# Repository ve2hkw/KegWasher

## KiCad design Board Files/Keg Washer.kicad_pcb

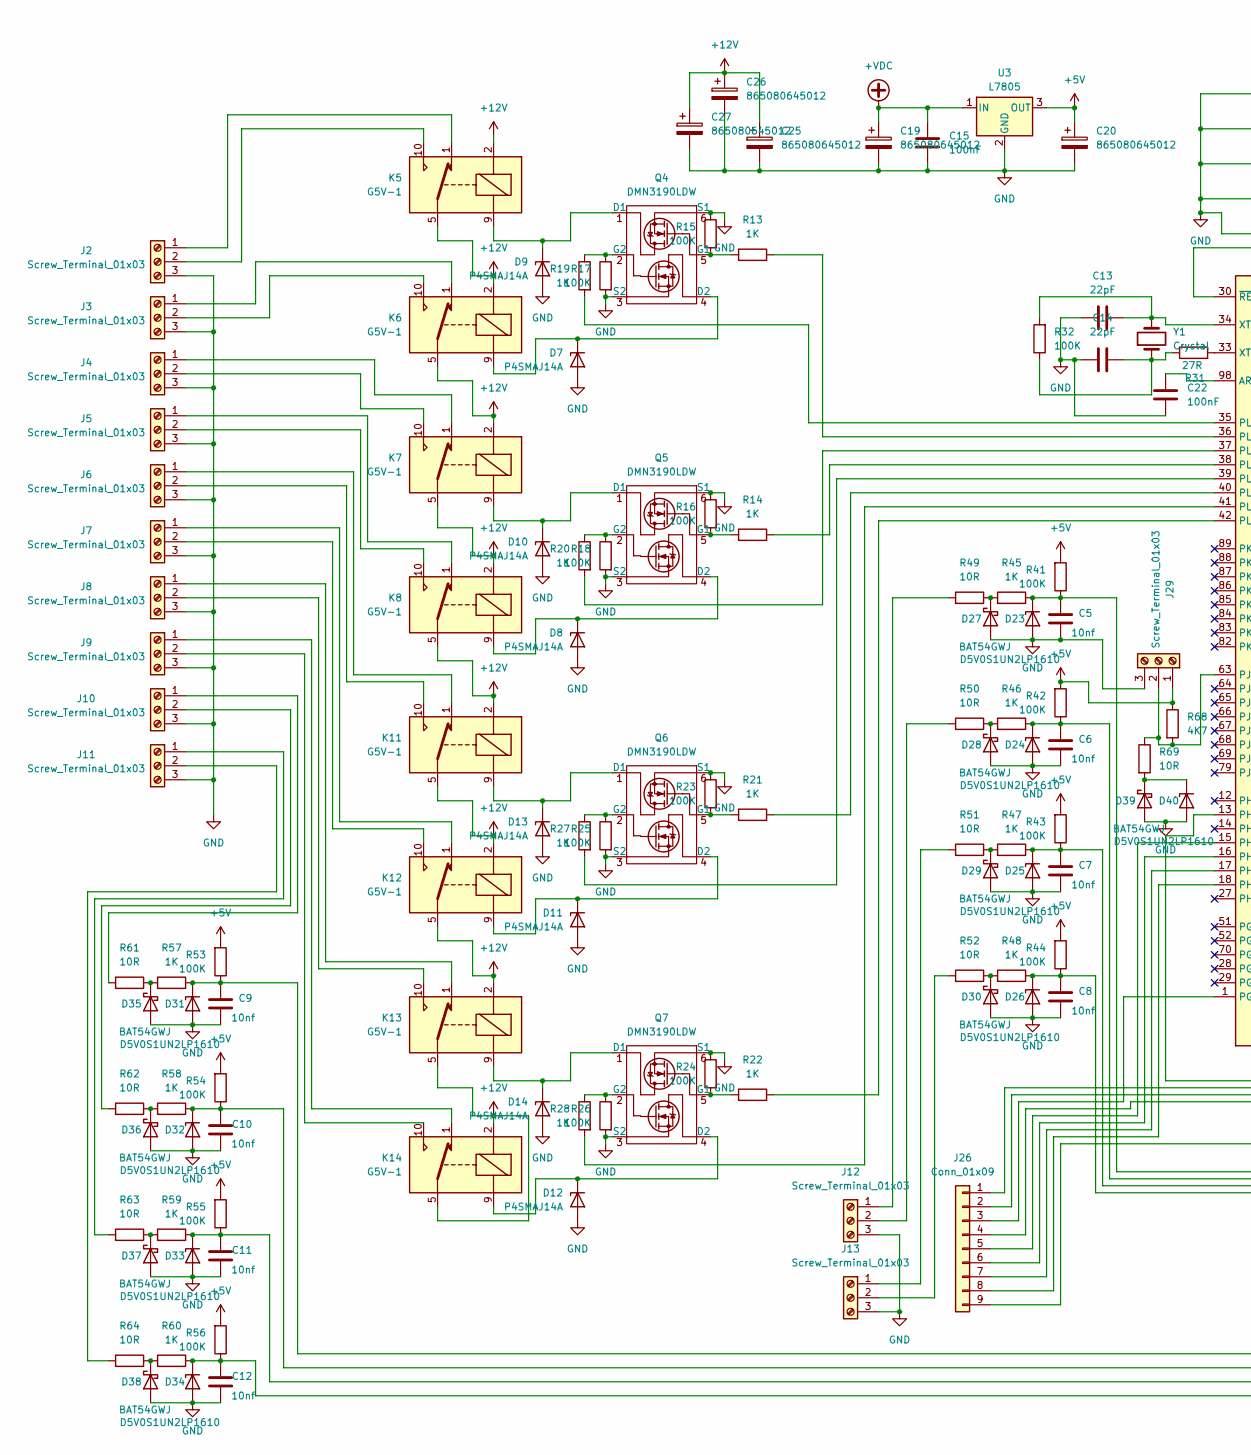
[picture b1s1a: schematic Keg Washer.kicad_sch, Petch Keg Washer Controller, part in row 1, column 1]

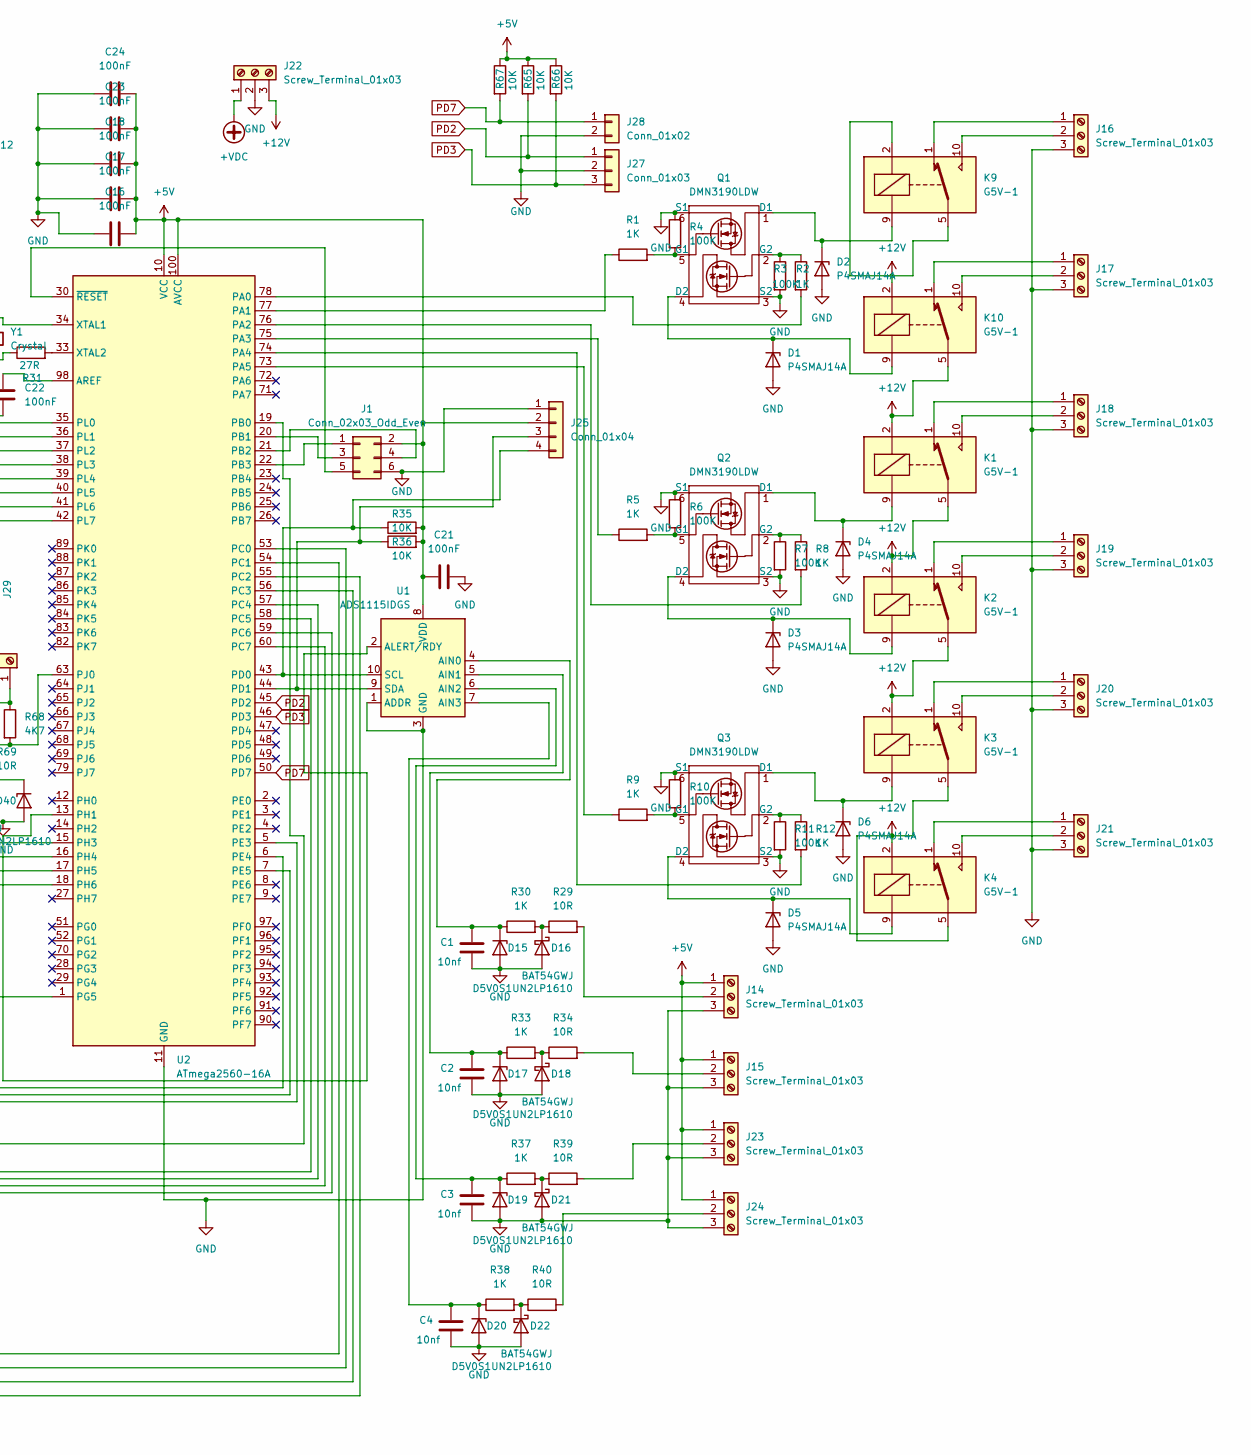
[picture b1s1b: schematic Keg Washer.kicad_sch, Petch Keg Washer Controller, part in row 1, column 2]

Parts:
C1, C2, C3, C4, C5, C6, C7, C8, C9, C10, C11, C12: 10nf; C_0805_2012Metric
C13, C14: 22pF; C_0805_2012Metric
C15, C16, C17, C18, C21, C22, C23, C24: 100nF; C_0805_2012Metric
C19, C20, C25, C26, C27: 865080645012; CP_Elec_6.3x7.7
D1, D2, D3, D4, D5, D6, D7, D8, D9, D10, D11, D12, D13, D14: P4SMAJ14A; D_SMA
D15, D17, D19, D20, D23, D24, D25, D26, D31, D32, D33, D34, D40: D5V0S1UN2LP1610; D_0603_1608Metric
D16, D18, D21, D22, D27, D28, D29, D30, D35, D36, D37, D38, D39: BAT54GWJ; D_SOD-123
J1: Conn_02x03_Odd_Even; PinHeader_2x03_P2.54mm_Vertical
J2, J3, J4, J5, J6, J7, J8, J9, J10, J11, J12, J13, J14, J15, J16, J17, J18, J19, J20, J21, J22, J23, J24, J29: Screw_Terminal_01x03; Altech_AK100_1x03_P5.00mm
J25: Conn_01x04; PinHeader_1x04_P2.54mm_Vertical
J26: Conn_01x09; PinHeader_1x09_P2.54mm_Vertical
J27: Conn_01x03; PinHeader_1x03_P2.54mm_Vertical
J28: Conn_01x02; PinHeader_1x02_P2.54mm_Vertical
K1, K2, K3, K4, K5, K6, K7, K8, K9, K10, K11, K12, K13, K14: G5V-1; Relay_SPDT_Omron_G5V-1
Q1, Q2, Q3, Q4, Q5, Q6, Q7: DMN3190LDW; SOT-363_SC-70-6
R1, R2, R5, R8, R9, R12, R13, R14, R19, R20, R21, R22, R27, R28, R30, R33, R37, R38, R45, R46, R47, R48, R57, R58, R59, R60: 1K; R_0805_2012Metric
R3, R4, R6, R7, R10, R11, R15, R16, R17, R18, R23, R24, R25, R26, R32, R41, R42, R43, R44, R53, R54, R55, R56: 100K; R_0805_2012Metric
R29, R34, R39, R40, R49, R50, R51, R52, R61, R62, R63, R64, R69: 10R; R_0805_2012Metric
R31: 27R; R_0805_2012Metric
R35, R36, R65, R66, R67: 10K; R_0805_2012Metric
R68: 4K7; R_0805_2012Metric
U1: ADS1115IDGS; TSSOP-10_3x3mm_P0.5mm
U2: ATmega2560-16A; TQFP-100_14x14mm_P0.5mm
U3: L7805; TO-220F-3_Vertical
Y1: Crystal; Crystal_SMD_ECS_CSM3X-2Pin_7.6x4.1mm

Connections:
+5V: C16.2, C17.2, C18.2, C20.1, C21.1, C23.2, C24.2, J1.2, J14.1, J15.1, J23.1, J24.1, J25.2, J29.1, R35.2, R36.2, R41.2, R42.2, R43.2, R44.2, R53.2, R54.2, R55.2, R56.2, R65.1, R66.1, R67.1, R68.1, U1.8 (VDD), U2.10 (VCC), U2.31 (VCC), U2.61 (VCC), U2.80 (VCC), U2.100 (AVCC), U3.3 (OUT)
+12V: C25.1, C26.1, C27.1, J22.3, K1.2, K1.5, K1.6, K2.2, K2.5, K2.6, K3.2, K3.5, K3.6, K4.2, K4.5, K4.6, K5.2, K5.5, K5.6, K6.2, K6.5, K6.6, K7.2, K7.5, K7.6, K8.2, K8.5, K8.6, K9.2, K9.5, K9.6, K10.2, K10.5, K10.6, K11.2, K11.5, K11.6, K12.2, K12.5, K12.6, K13.2, K13.5, K13.6, K14.2, K14.5, K14.6
+VDC: C15.1, C19.1, J22.1, U3.1 (IN)
GND: C1.2, C2.2, C3.2, C4.2, C5.2, C6.2, C7.2, C8.2, C9.2, C10.2, C11.2, C12.2, C13.1, C14.1, C15.2, C16.1, C17.1, C18.1, C19.2, C20.2, C21.2, C22.1, C23.1, C24.1, C25.2, C26.2, C27.2, D1.2 (A), D2.2 (A), D3.2 (A), D4.2 (A), D5.2 (A), D6.2 (A), D7.2 (A), D8.2 (A), D9.2 (A), D10.2 (A), D11.2 (A), D12.2 (A), D13.2 (A), D14.2 (A), D15.2 (A), D16.2 (A), D17.2 (A), D18.2 (A), D19.2 (A), D20.2 (A), D21.2 (A), D22.2 (A), D23.2 (A), D24.2 (A), D25.2 (A), D26.2 (A), D27.2 (A), D28.2 (A), D29.2 (A), D30.2 (A), D31.2 (A), D32.2 (A), D33.2 (A), D34.2 (A), D35.2 (A), D36.2 (A), D37.2 (A), D38.2 (A), D39.2 (A), D40.2 (A), J1.6, J2.3, J3.3, J4.3, J5.3, J6.3, J7.3, J8.3, J9.3, J10.3, J11.3, J12.3, J13.3, J14.3, J15.3, J16.3, J17.3, J18.3, J19.3, J20.3, J21.3, J22.2, J23.3, J24.3, J25.1, J27.2, J28.2, J29.3, Q1.3 (S2), Q1.6 (S1), Q2.3 (S2), Q2.6 (S1), Q3.3 (S2), Q3.6 (S1), Q4.3 (S2), Q4.6 (S1), Q5.3 (S2), Q5.6 (S1), Q6.3 (S2), Q6.6 (S1), Q7.3 (S2), Q7.6 (S1), R3.2, R4.1, R6.1, R7.2, R10.1, R11.2, R15.1, R16.1, R17.2, R18.2, R23.1, R24.1, R25.2, R26.2, U1.1 (ADDR), U1.3 (GND), U2.11 (GND), U2.32 (GND), U2.62 (GND), U2.81 (GND), U2.99 (GND), U3.2 (GND)
unnamed: C14.2, R31.1, R32.1, Y1.1
unnamed: D1.1 (K), K10.9, Q1.4 (D2)
unnamed: D2.1 (K), K9.9, Q1.1 (D1)
unnamed: D3.1 (K), K2.9, Q2.4 (D2)
unnamed: D4.1 (K), K1.9, Q2.1 (D1)
unnamed: D5.1 (K), K4.9, Q3.4 (D2)
unnamed: D6.1 (K), K3.9, Q3.1 (D1)
unnamed: D7.1 (K), K6.9, Q4.4 (D2)
unnamed: D8.1 (K), K8.9, Q5.4 (D2)
unnamed: D9.1 (K), K5.9, Q4.1 (D1)
unnamed: D10.1 (K), K7.9, Q5.1 (D1)
unnamed: D11.1 (K), K12.9, Q6.4 (D2)
unnamed: D12.1 (K), K14.9, Q7.4 (D2)
unnamed: D13.1 (K), K11.9, Q6.1 (D1)
unnamed: D14.1 (K), K13.9, Q7.1 (D1)
unnamed: C1.1, D15.1 (K), R30.1, U1.4 (AIN0)
unnamed: D16.1 (K), R29.1, R30.2
unnamed: C2.1, D17.1 (K), R33.1, U1.5 (AIN1)
unnamed: D18.1 (K), R33.2, R34.1
unnamed: C3.1, D19.1 (K), R37.1, U1.6 (AIN2)
unnamed: C4.1, D20.1 (K), R38.1, U1.7 (AIN3)
unnamed: D21.1 (K), R37.2, R39.1
unnamed: D22.1 (K), R38.2, R40.1
unnamed: C5.1, D23.1 (K), R41.1, R45.1, U2.58 (PC5)
unnamed: C6.1, D24.1 (K), R42.1, R46.1, U2.57 (PC4)
unnamed: C7.1, D25.1 (K), R43.1, R47.1, U2.60 (PC7)
unnamed: C8.1, D26.1 (K), R44.1, R48.1, U2.59 (PC6)
unnamed: D27.1 (K), R45.2, R49.1
unnamed: D28.1 (K), R46.2, R50.1
unnamed: D29.1 (K), R47.2, R51.1
unnamed: D30.1 (K), R48.2, R52.1
unnamed: C9.1, D31.1 (K), R53.1, R57.1, U2.54 (PC1)
unnamed: C10.1, D32.1 (K), R54.1, R58.1, U2.53 (PC0)
unnamed: C11.1, D33.1 (K), R55.1, R59.1, U2.56 (PC3)
unnamed: C12.1, D34.1 (K), R56.1, R60.1, U2.55 (PC2)
unnamed: D35.1 (K), R57.2, R61.1
unnamed: D36.1 (K), R58.2, R62.1
unnamed: D37.1 (K), R59.2, R63.1
unnamed: D38.1 (K), R60.2, R64.1
unnamed: D39.1 (K), D40.1 (K), R69.2
unnamed: J1.1, U2.22 (PB3)
unnamed: J1.3, U2.20 (PB1)
unnamed: J1.4, U2.21 (PB2)
unnamed: J1.5, U2.30 (~RESET)
unnamed: J2.1, K5.1
unnamed: J2.2, K5.10
unnamed: J3.1, K6.1
unnamed: J3.2, K6.10
unnamed: J4.1, K7.1
unnamed: J4.2, K7.10
unnamed: J5.1, K8.1
unnamed: J5.2, K8.10
unnamed: J6.1, K11.1
unnamed: J6.2, K11.10
unnamed: J7.1, K12.1
unnamed: J7.2, K12.10
unnamed: J8.1, K13.1
unnamed: J8.2, K13.10
unnamed: J9.1, K14.1
unnamed: J9.2, K14.10
unnamed: J10.1, R61.2
unnamed: J10.2, R62.2
unnamed: J11.1, R63.2
unnamed: J11.2, R64.2
unnamed: J12.1, R49.2
unnamed: J12.2, R50.2
unnamed: J13.1, R51.2
unnamed: J13.2, R52.2
unnamed: J14.2, R29.2
unnamed: J15.2, R34.2
unnamed: J16.1, K9.1
unnamed: J16.2, K9.10
unnamed: J17.1, K10.1
unnamed: J17.2, K10.10
unnamed: J18.1, K1.1
unnamed: J18.2, K1.10
unnamed: J19.1, K2.1
unnamed: J19.2, K2.10
unnamed: J20.1, K3.1
unnamed: J20.2, K3.10
unnamed: J21.1, K4.1
unnamed: J21.2, K4.10
unnamed: J23.2, R39.2
unnamed: J24.2, R40.2
unnamed: J25.3, R36.1, U1.9 (SDA), U2.44 (PD1)
unnamed: J25.4, R35.1, U1.10 (SCL), U2.43 (PD0)
unnamed: J26.1, U2.6 (PE4)
unnamed: J26.2, U2.7 (PE5)
unnamed: J26.3, U2.1 (PG5)
unnamed: J26.4, U2.5 (PE3)
unnamed: J26.5, U2.15 (PH3)
unnamed: J26.6, U2.16 (PH4)
unnamed: J26.7, U2.17 (PH5)
unnamed: J26.8, U2.18 (PH6)
unnamed: J26.9, U2.19 (PB0)
unnamed: J29.2, R68.2, R69.1, U2.63 (PJ0)
unnamed: Q1.5 (G1), R1.2, R4.2
unnamed: Q1.2 (G2), R2.1, R3.1
unnamed: Q2.5 (G1), R5.2, R6.2
unnamed: Q2.2 (G2), R7.1, R8.1
unnamed: Q3.5 (G1), R9.2, R10.2
unnamed: Q3.2 (G2), R11.1, R12.1
unnamed: Q4.5 (G1), R13.2, R15.2
unnamed: Q4.2 (G2), R17.1, R19.1
unnamed: Q5.5 (G1), R14.2, R16.2
unnamed: Q5.2 (G2), R18.1, R20.1
unnamed: Q6.5 (G1), R21.2, R23.2
unnamed: Q6.2 (G2), R25.1, R27.1
unnamed: Q7.5 (G1), R22.2, R24.2
unnamed: Q7.2 (G2), R26.1, R28.1
unnamed: U1.2 (ALERT/RDY), U2.13 (PH1)
unnamed: C22.2, U2.98 (AREF)
unnamed: R2.2, U2.78 (PA0)
unnamed: R1.1, U2.77 (PA1)
unnamed: R8.2, U2.76 (PA2)
unnamed: R5.1, U2.75 (PA3)
unnamed: R12.2, U2.74 (PA4)
unnamed: R9.1, U2.73 (PA5)
unnamed: R19.2, U2.35 (PL0)
unnamed: R13.1, U2.36 (PL1)
unnamed: R20.2, U2.37 (PL2)
unnamed: R14.1, U2.38 (PL3)
unnamed: R27.2, U2.39 (PL4)
unnamed: R21.1, U2.40 (PL5)
unnamed: R28.2, U2.41 (PL6)
unnamed: R22.1, U2.42 (PL7)
unnamed: C13.2, R32.2, U2.34 (XTAL1), Y1.2
unnamed: R31.2, U2.33 (XTAL2)
PD2: J27.1, R65.2, U2.45 (PD2)
PD3: J27.3, R66.2, U2.46 (PD3)
PD7: J28.1, R67.2, U2.50 (PD7)

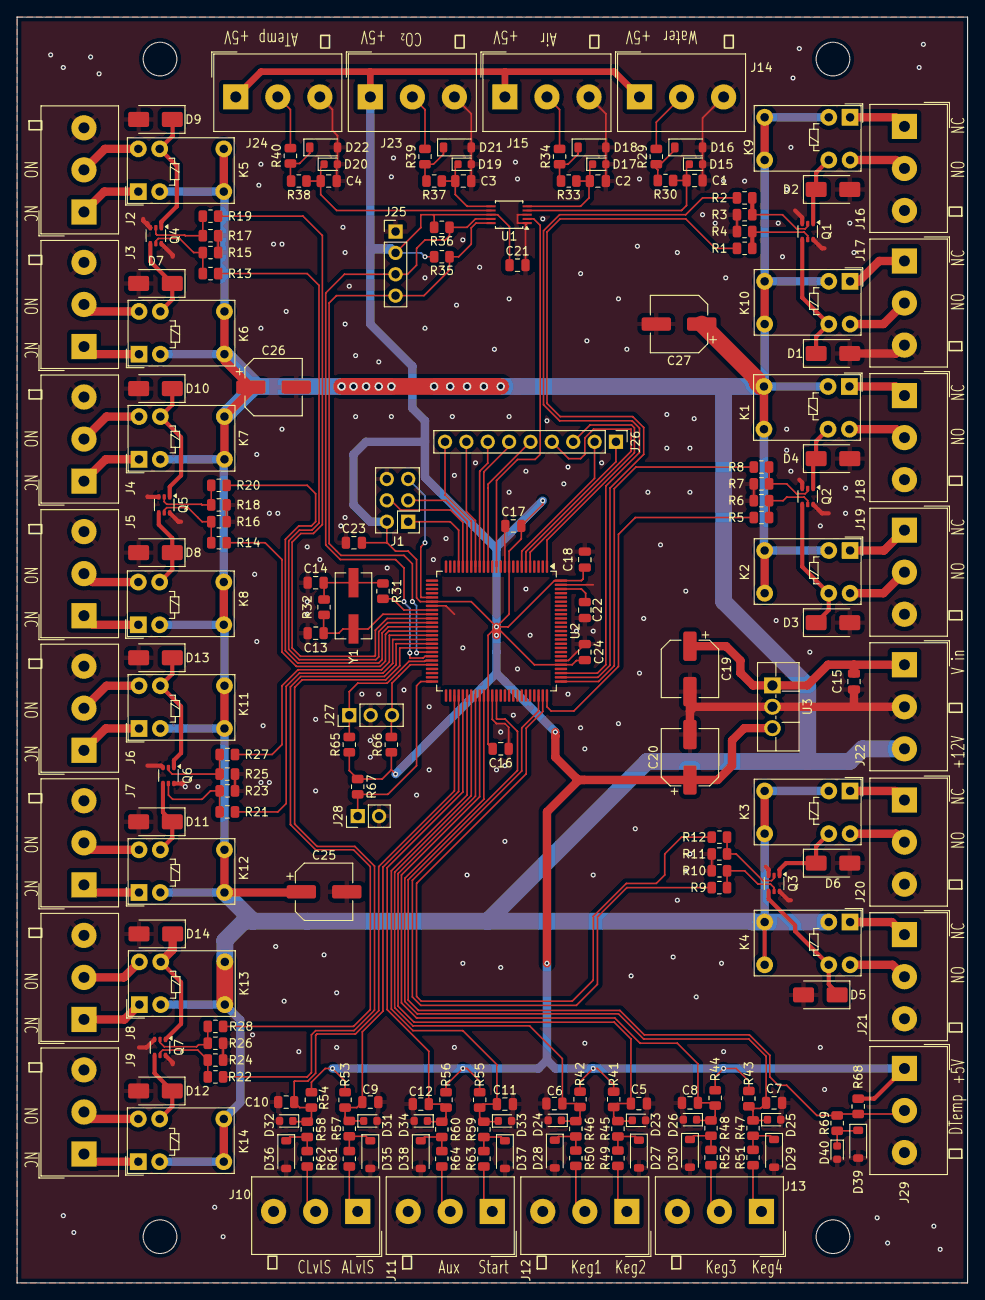
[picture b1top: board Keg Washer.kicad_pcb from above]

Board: 2 copper layers, 113.0 x 150.5 mm, 190 parts (0 on the bottom side), 135 nets.

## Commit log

2025-02-08 inital commit
2025-02-08 Added License
2025-02-11 Code update
2025-02-11 Added a symlink to the board files directory to test
2025-02-11 Added board files
2025-02-11 Added Board files (for realz)
